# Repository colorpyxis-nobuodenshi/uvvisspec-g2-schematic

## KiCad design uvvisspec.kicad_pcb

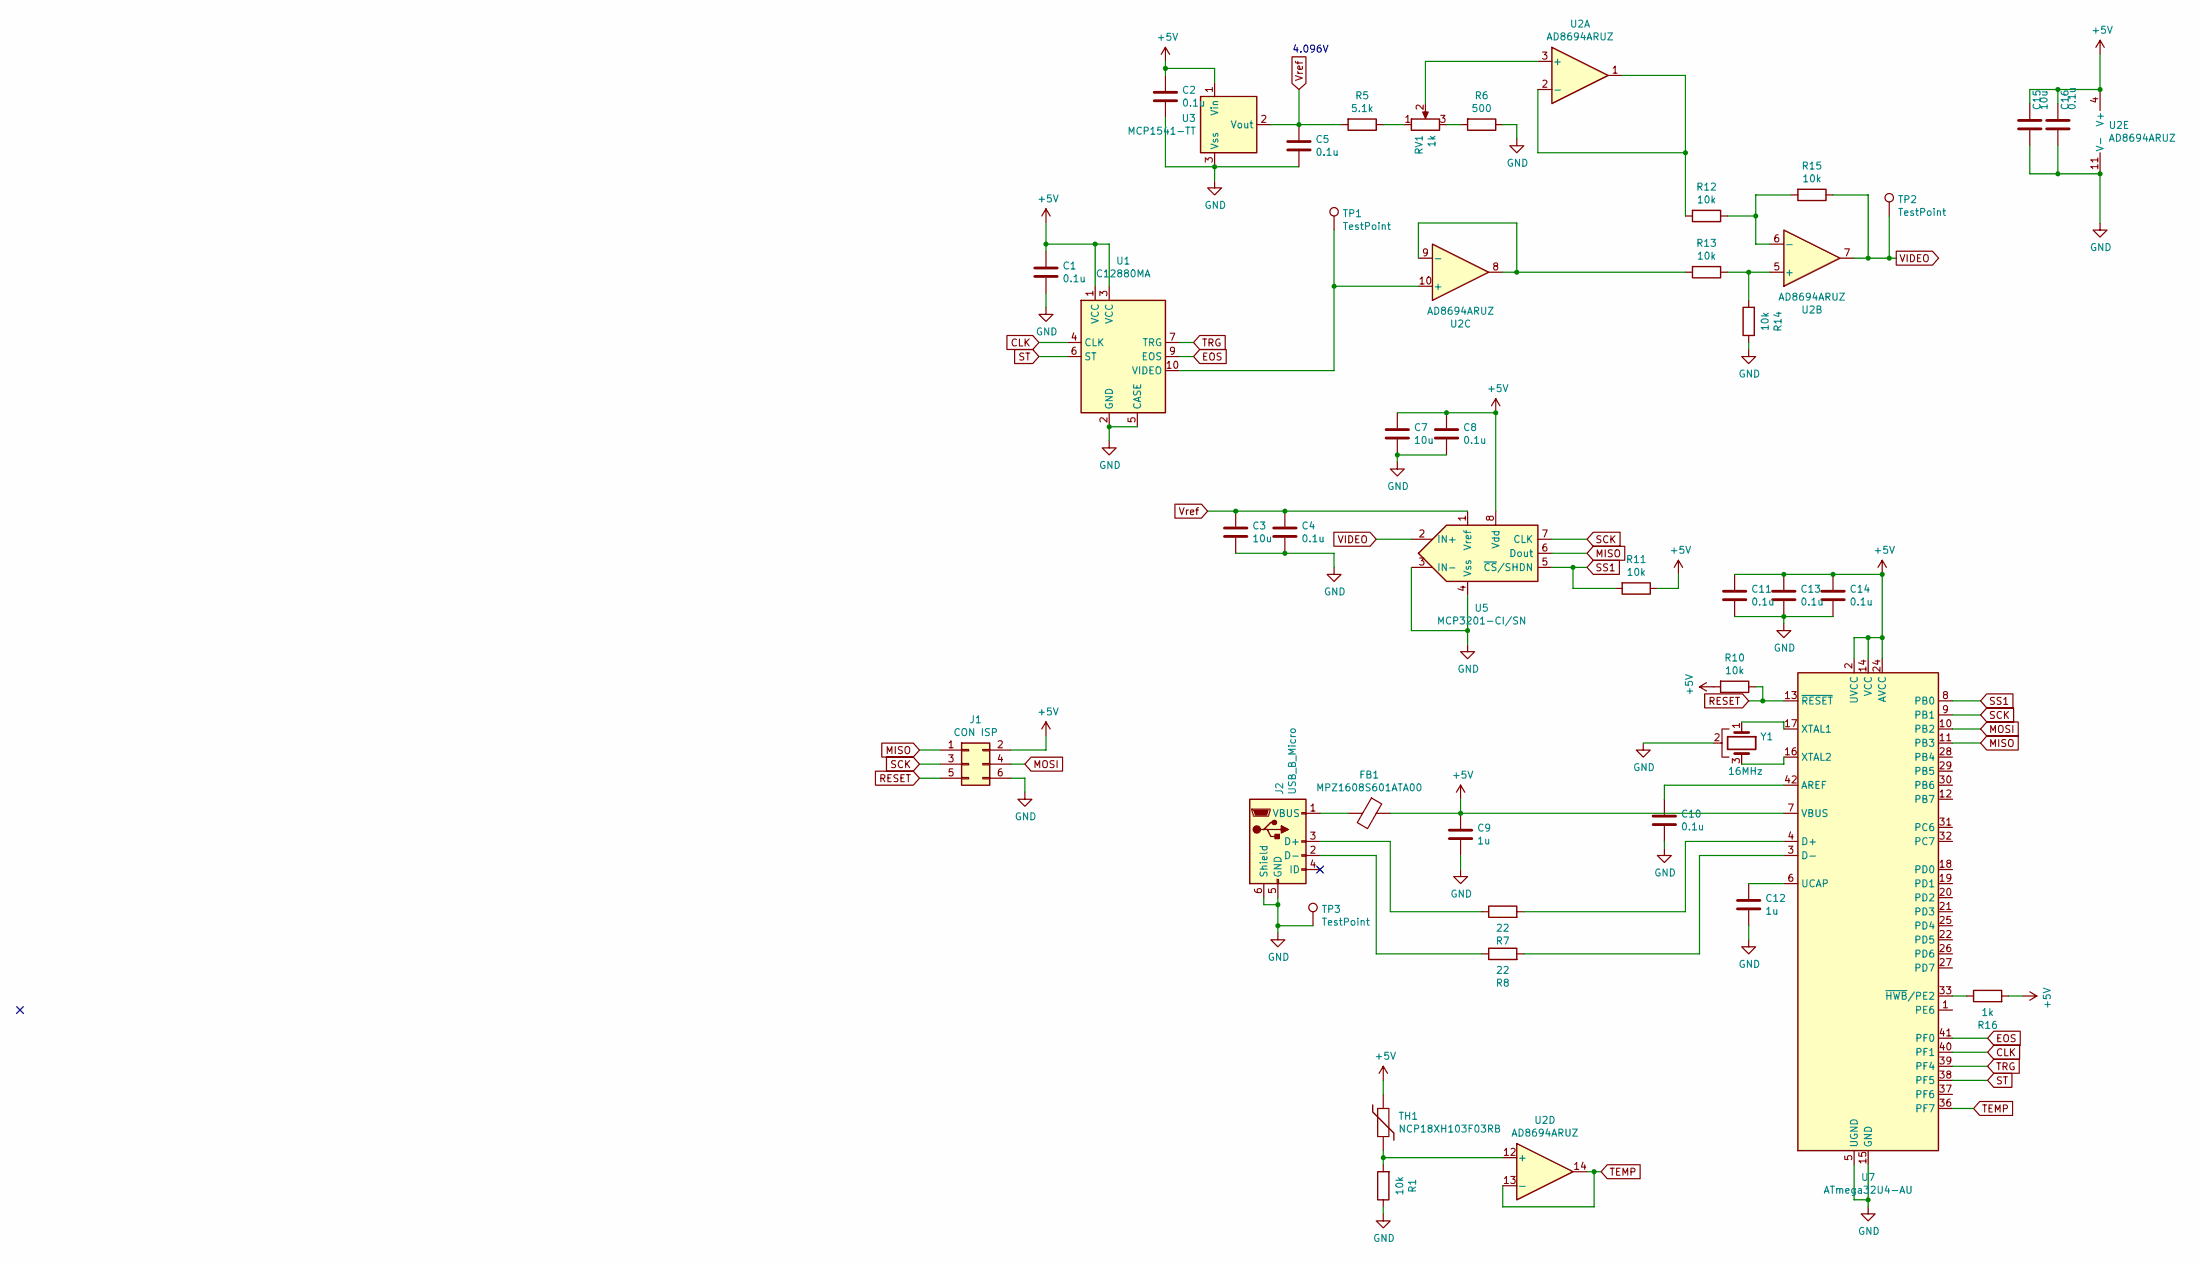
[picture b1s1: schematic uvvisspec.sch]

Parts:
C1, C2, C4, C5, C8, C10, C11, C13, C14, C16: 0.1u; C_0603_1608Metric
C3, C7, C15: 10u; C_0603_1608Metric
C9, C12: 1u; C_0603_1608Metric
FB1: MPZ1608S601ATA00; L_0603_1608Metric
J1: CON ISP; PinHeader_2x03_P2.54mm_Vertical
J2: USB_B_Micro; HIROSE_ZX62D-B-5PA8
R1, R10, R11, R12, R13, R14, R15: 10k; R_0603_1608Metric
R5: 5.1k; R_0603_1608Metric
R6: 500; R_0603_1608Metric
R7, R8: 22; R_0603_1608Metric
R16: 1k; R_0603_1608Metric
RV1: 1k; Potentiometer_Bourns_3214W_Vertical
TH1: NCP18XH103F03RB; R_0603_1608Metric
TP1, TP2, TP3: TestPoint; TestPoint_Pad_1.0x1.0mm
U1: C12880MA; Hamamatsu_C12880
U2: AD8694ARUZ; TSSOP-14_4.4x5mm_P0.65mm
U3: MCP1541-TT; SOT-23
U5: MCP3201-CI/SN; SOIC-8_3.9x4.9mm_P1.27mm
U7: ATmega32U4-AU; TQFP-44_10x10mm_P0.8mm
Y1: 16MHz; Resonator_SMD_muRata_CSTxExxV-3Pin_3.0x1.1mm

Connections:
+5V: C1.1, C2.1, C7.1, C8.1, C9.1, C11.1, C13.1, C14.1, C15.1, C16.1, FB1.1, J1.2, R10.2, R11.1, R16.2, TH1.1, U1.1 (VCC), U1.3 (VCC), U2.4 (V+), U3.1 (Vin), U5.8 (Vdd), U7.2 (UVCC), U7.7 (VBUS), U7.14 (VCC), U7.24 (AVCC), U7.34 (VCC), U7.44 (AVCC)
CLK: U1.4 (CLK), U7.40 (PF1)
EOS: U1.9 (EOS), U7.41 (PF0)
GND: C1.2, C2.2, C3.2, C4.2, C5.2, C7.2, C8.2, C9.2, C10.2, C11.2, C12.2, C13.2, C14.2, C15.2, C16.2, J1.6, J2.5 (GND), J2.6 (Shield), R1.1, R6.1, R14.1, TP3.1, U1.2 (GND), U1.5 (CASE), U2.11 (V-), U3.3 (Vss), U5.3 (IN-), U5.4 (Vss), U7.5 (UGND), U7.15 (GND), U7.23 (GND), U7.35 (GND), U7.43 (GND), Y1.2
MISO: J1.1, U5.6 (Dout), U7.11 (PB3)
MOSI: J1.4, U7.10 (PB2)
unnamed: C10.1, U7.42 (AREF)
unnamed: C12.1, U7.6 (UCAP)
unnamed: FB1.2, J2.1 (VBUS)
unnamed: J2.2 (D-), R8.1
unnamed: J2.3 (D+), R7.1
unnamed: R1.2, TH1.2, U2.12 (+)
unnamed: R5.1, RV1.1
unnamed: R6.2, RV1.3
unnamed: R7.2, U7.4 (D+)
unnamed: R8.2, U7.3 (D-)
unnamed: R12.1, R15.2, U2.6 (-)
unnamed: R12.2, U2.1, U2.2 (-)
unnamed: R13.1, R14.2, U2.5 (+)
unnamed: R13.2, U2.8, U2.9 (-)
unnamed: R16.1, U7.33 (~HWB~/PE2)
unnamed: RV1.2, U2.3 (+)
unnamed: TP1.1, U1.10 (VIDEO), U2.10 (+)
unnamed: U7.16 (XTAL2), Y1.3
unnamed: U7.17 (XTAL1), Y1.1
RESET: J1.5, R10.1, U7.13 (~RESET)
SCK: J1.3, U5.7 (CLK), U7.9 (PB1)
SS1: R11.2, U5.5 (~CS~/SHDN), U7.8 (PB0)
ST: U1.6 (ST), U7.38 (PF5)
TEMP: U2.13 (-), U2.14, U7.36 (PF7)
TRG: U1.7 (TRG), U7.39 (PF4)
VIDEO: R15.1, TP2.1, U2.7, U5.2 (IN+)
Vref: C3.1, C4.1, C5.1, R5.2, U3.2 (Vout), U5.1 (Vref)

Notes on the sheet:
4.096V

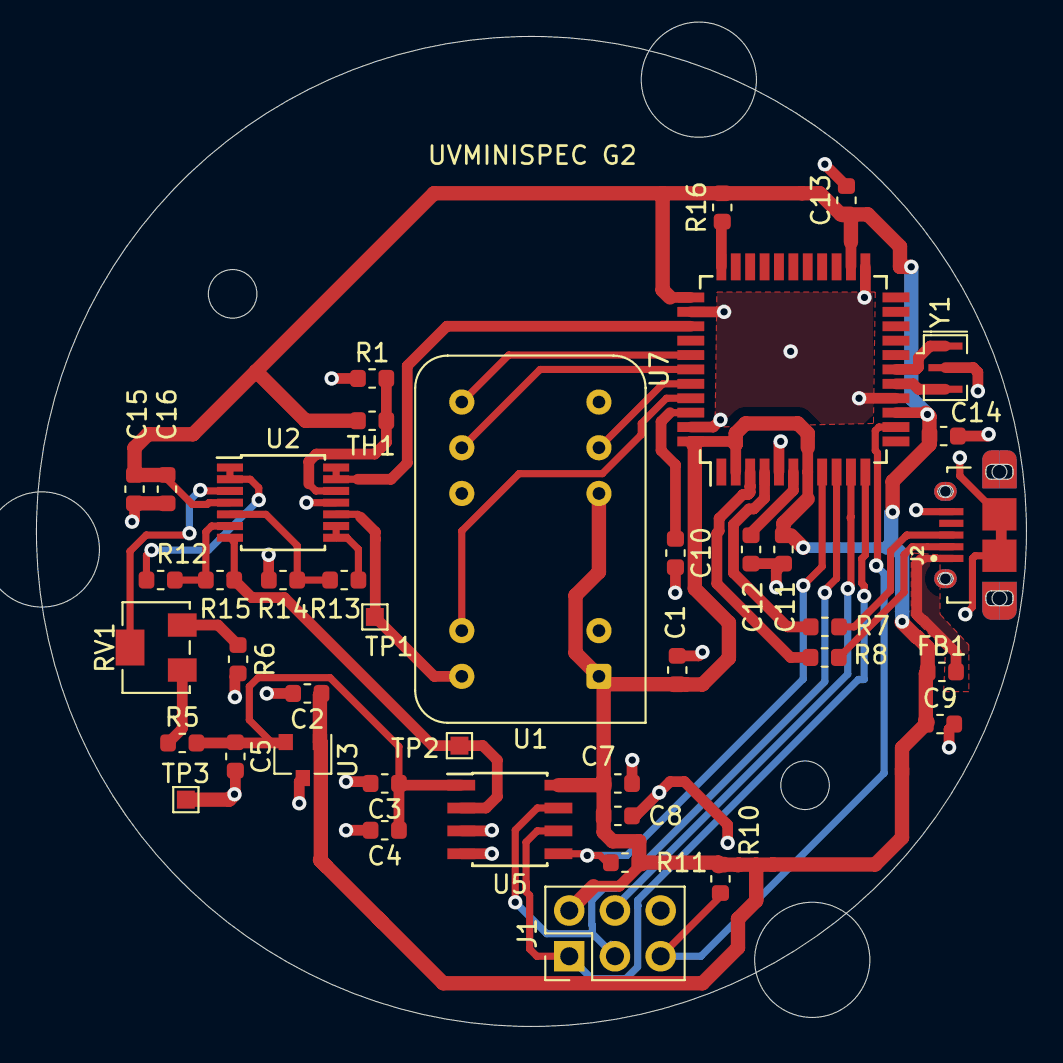
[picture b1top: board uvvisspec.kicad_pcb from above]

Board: 2 copper layers, 55.0 x 55.0 mm, 43 parts (0 on the bottom side), 33 nets.

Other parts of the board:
h1, h2: MountingHole_2.7mm_M2.5

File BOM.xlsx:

CP150 UVMINISPECTROMETER_G2 電子回路基板部品表デンシカイロキバンブヒンヒョウ
 |  |  |  |  | ノブオ電子株式会社デンシカブシキガイシャ
Ref | 品名ヒンメイ | 形式ケイシキ | 定格テイカク | メーカ- | 個数コスウ
> C3, C7, C15 | 積層セラミックコンデンサセキソウ | GRM188R6YA106MA73 | 10u |  | 3
> C9, C12 | 積層セラミックコンデンサセキソウ | GRM188R71E105KA12 | 1u |  | 2
> C1, C2, C4, C5, C8, C10, C11, C13, C14, C16 | 積層セラミックコンデンサセキソウ | GRM188F11H104ZA01 | 0.1u |  | 10
FB1 | フェライトコアビーズ | MPZ1608S601ATA00 |  |  | 1
J1 | コネクタ | 2.54mmPINHEADER |  |  | 1
J2 | コネクタ | ZX62-B-5PA8 |  |  | 1
R5 | チップ抵抗器テイコウキ | RK73B1JTTD512J | 5.1k |  | 1
R6 | チップ抵抗器テイコウキ | RK73H1JTTD3000F | 500 |  | 1
> R7, R8 | チップ抵抗器テイコウキ | RK73H1JTTD22R0F | 22 |  | 2
> R1, R10-R15 | チップ抵抗器テイコウキ |  | 10k |  | 7
R16 | チップ抵抗器テイコウキ | 804-8845 | 1k |  | 1
RV1 | 可変抵抗器カヘンテイコウキ | 3214W-1-102E | 1k |  | 1
TH1 | サーミスタ | NCP18XH103F03RB |  |  | 1
> TP1, TP2 | テストポイント |  |  |  | 2
U1 | IC | C12880MA |  |  | 1
U2 | IC | AD8694ARUZ |  |  | 1
U3 | IC | MCP1541T-I/TT |  |  | 1
U5 | IC | MCP3201-CI/SN |  |  | 1
U7 | IC | ATmega32U4-AU |  |  | 1
Y1 | IC | CSTNE16M0V530000R0 | 16MHz |  | 1

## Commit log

2023-03-09 2023/3/9
